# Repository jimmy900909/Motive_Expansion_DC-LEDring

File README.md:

# Motive_Expansion_DC-LEDring

Author:Wei Ching Ling 25/01/2026

This is the PCB rings, 3D printed holding frame and system setup instruction for Motive DC LED source, which can eliminate EMI noise if you are recording vulnerable signal (etc. brain signal) at the same time. This model was tested and the size fit for cameras Primex 41 and Prime 17

### Bill of Materials (BOM)
* **LINOVISION 90W PoE++ Splitter** - amount: 1
* **Endark 12 way fuse Block** - amount: 1
* **ORSRAM SFH 4556-AW 860nm Infrared LED** - amount: 30 / per ring
* **1W 20Ohm Resistors** - amount: 2 / per ring
* **PCB ring** - amount: 1 / per ring
* **3D print frame** - amount: 1 / per ring

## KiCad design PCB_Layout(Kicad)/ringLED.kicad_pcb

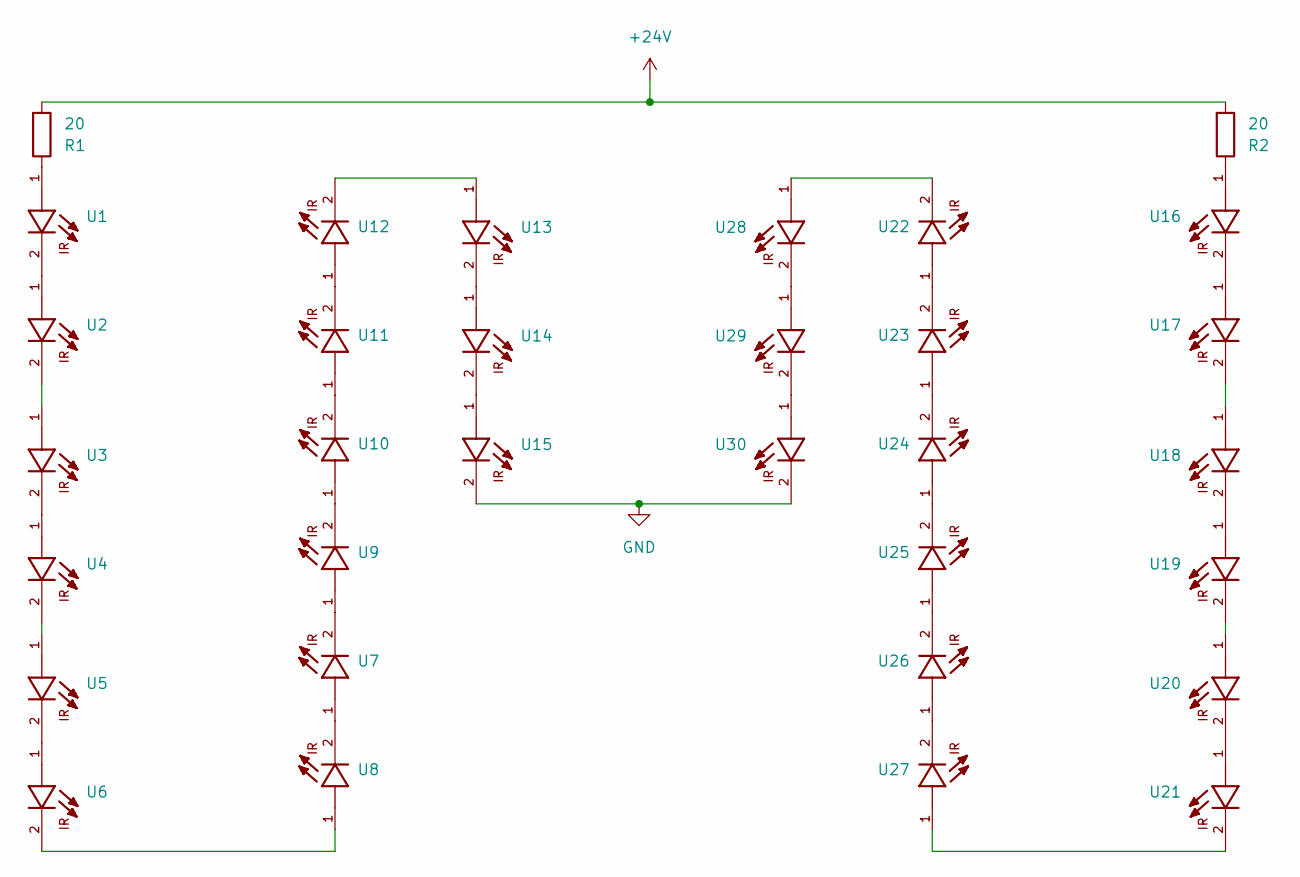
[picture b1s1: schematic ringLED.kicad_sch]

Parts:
R1, R2: 20; R_Axial_DIN0309_L9.0mm_D3.2mm_P12.70mm_Horizontal
U1, U2, U3, U4, U5, U6, U7, U8, U9, U10, U11, U12, U13, U14, U15, U16, U17, U18, U19, U20, U21, U22, U23, U24, U25, U26, U27, U28, U29, U30: LED_D5.0mm

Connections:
GND: U15.2, U30.2
unnamed: R1.1, U1.1
unnamed: R1.2, R2.2
unnamed: R2.1, U16.1
unnamed: U1.2, U2.1
unnamed: U2.2, U3.1
unnamed: U3.2, U4.1
unnamed: U4.2, U5.1
unnamed: U5.2, U6.1
unnamed: U6.2, U8.1
unnamed: U7.1, U8.2
unnamed: U7.2, U9.1
unnamed: U9.2, U10.1
unnamed: U10.2, U11.1
unnamed: U11.2, U12.1
unnamed: U12.2, U13.1
unnamed: U13.2, U14.1
unnamed: U14.2, U15.1
unnamed: U16.2, U17.1
unnamed: U17.2, U18.1
unnamed: U18.2, U19.1
unnamed: U19.2, U20.1
unnamed: U20.2, U21.1
unnamed: U21.2, U27.1
unnamed: U22.1, U23.2
unnamed: U22.2, U28.1
unnamed: U23.1, U24.2
unnamed: U24.1, U25.2
unnamed: U25.1, U26.2
unnamed: U26.1, U27.2
unnamed: U28.2, U29.1
unnamed: U29.2, U30.1

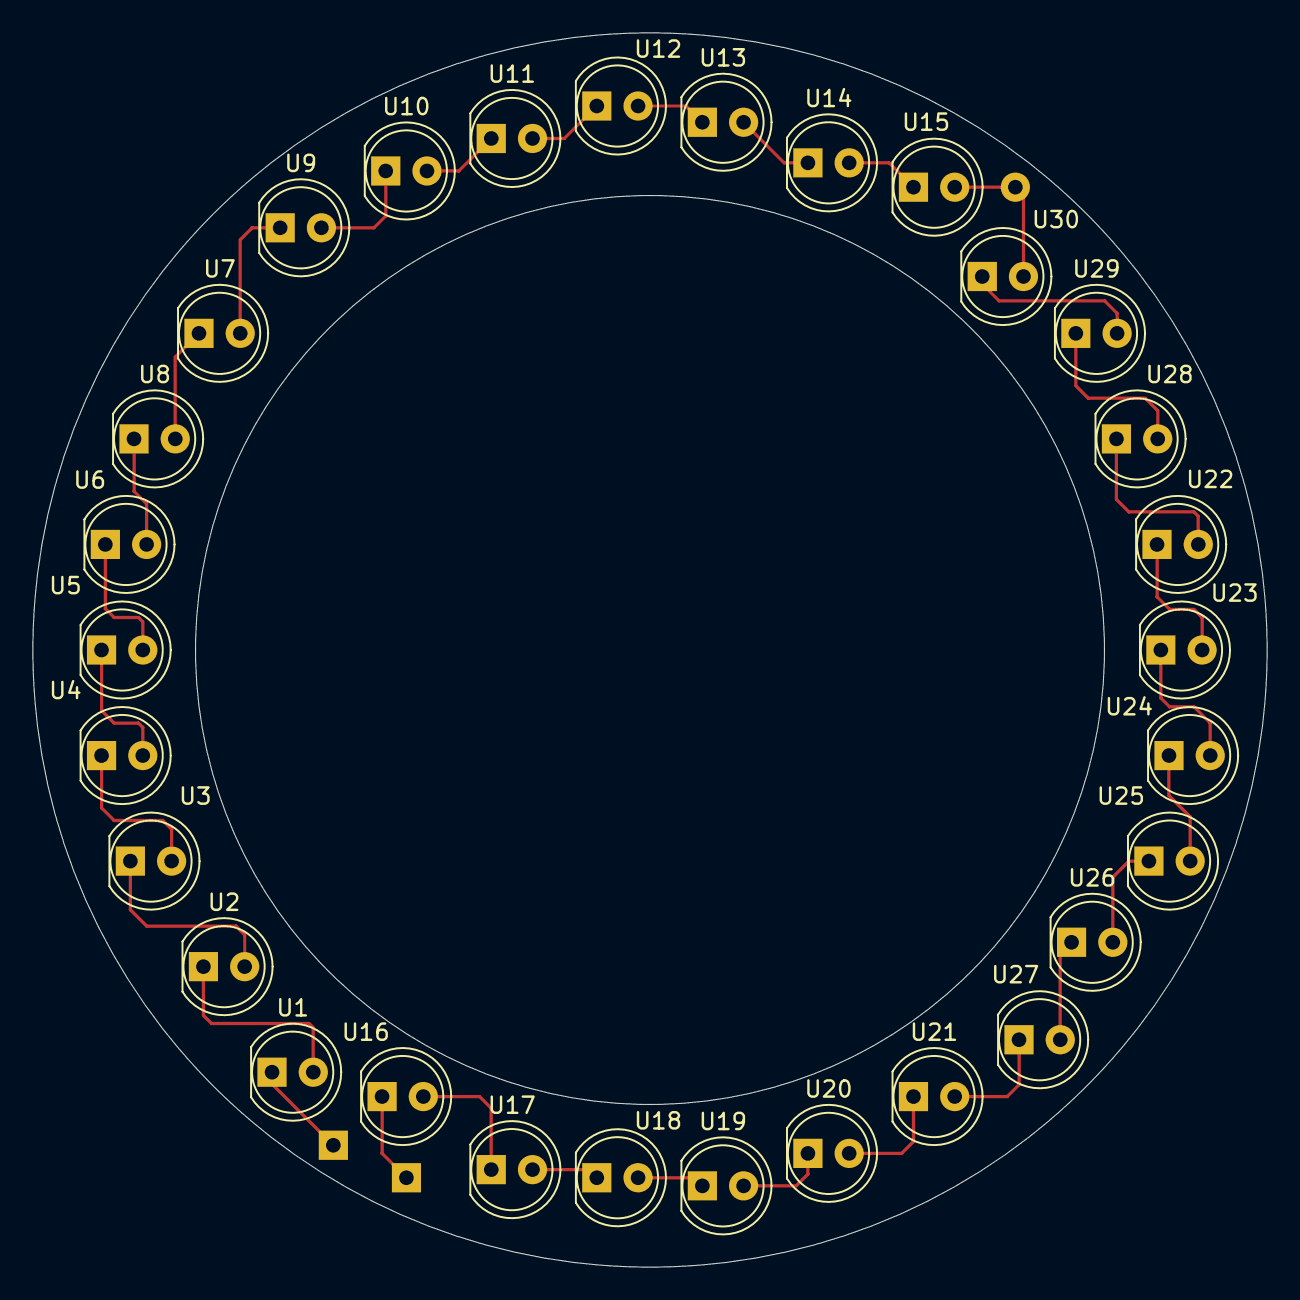
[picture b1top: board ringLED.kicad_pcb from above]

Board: 2 copper layers, 76.0 x 76.0 mm, 30 parts (0 on the bottom side), 29 nets.

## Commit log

2026-01-26 Update README with author and instruction clarification
2026-01-26 Update README with BOM and additional details
    Added BOM and clarified the content of the README.
2026-01-26 Update README with additional details and clarifications
    Clarified the description and added camera compatibility information.
2026-02-27 Add images and author information to README
2026-02-27 Revise BOM section in README.md
    Updated the Bill of Materials (BOM) section for clarity and formatting.
2026-02-27 Update README.md with additional images
